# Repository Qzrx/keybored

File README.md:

# keybored
I'm bored. Let's make a keyboard!

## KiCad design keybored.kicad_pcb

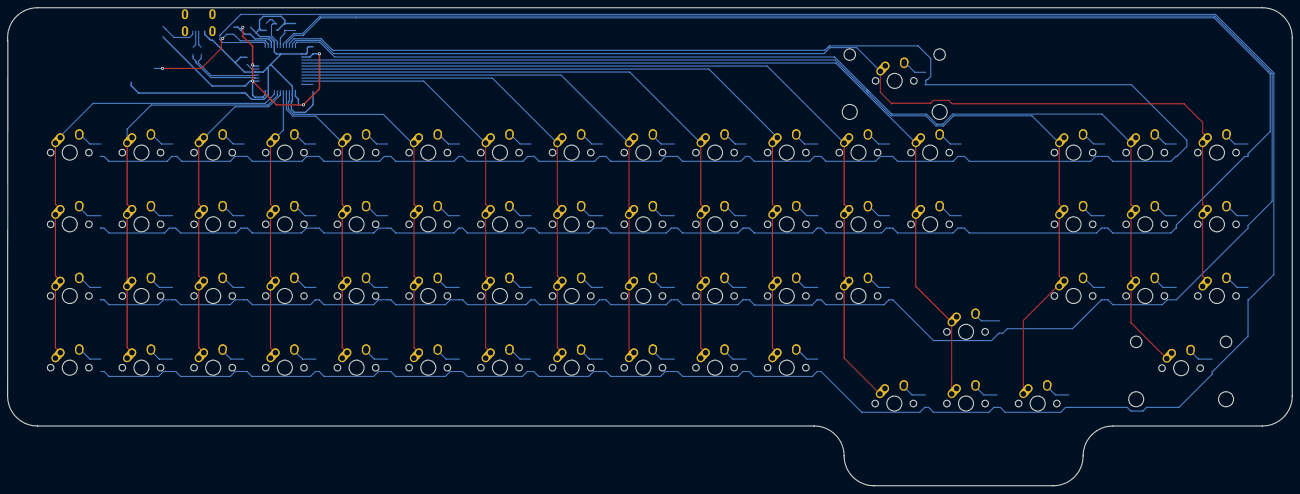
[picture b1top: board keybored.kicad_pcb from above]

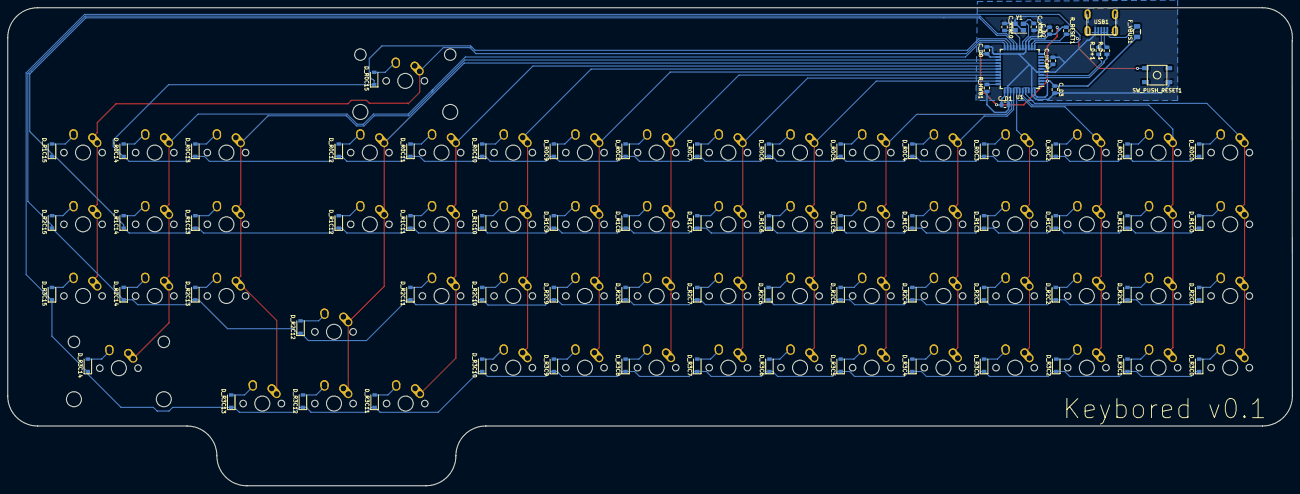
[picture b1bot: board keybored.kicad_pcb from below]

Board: 2 copper layers, 341.3 x 127.0 mm, 144 parts (80 on the bottom side), 96 nets.

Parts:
C_D0, C_D1, C_D2: 0.1uF; C_0805_2012Metric
C_D3: 10uF; C_0805_2012Metric
C_UCAP1: 1uF; C_0805_2012Metric
C_XTAL0, C_XTAL1: 22pF; C_0805_2012Metric
D_R0C0, D_R0C1, D_R0C2, D_R0C3, D_R0C4, D_R0C5, D_R0C6, D_R0C7, D_R0C8, D_R0C9, D_R0C10, D_R0C11, D_R0C12, D_R0C13, D_R0C14, D_R0C15, D_R1C0, D_R1C1, D_R1C2, D_R1C3, D_R1C4, D_R1C5, D_R1C6, D_R1C7, D_R1C8, D_R1C9, D_R1C10, D_R1C11, D_R1C12, D_R1C13, D_R1C14, D_R1C15, D_R2C0, D_R2C1, D_R2C2, D_R2C3, D_R2C4, D_R2C5, D_R2C6, D_R2C7, D_R2C8, D_R2C9, D_R2C10, D_R2C11, D_R2C12, D_R2C13, D_R2C14, D_R2C15, D_R3C0, D_R3C1, D_R3C2, D_R3C3, D_R3C4, D_R3C5, D_R3C6, D_R3C7, D_R3C8, D_R3C9, D_R3C10, D_R3C11, D_R3C12, D_R3C13, D_R3C14, D_R3C15: Diode; D_SOD-123
F_VBUS1: 500mA; Fuse_1206_3216Metric
MX_R0C0_ESC1, MX_R0C1_Q1, MX_R0C2_W1, MX_R0C3_E1, MX_R0C4_R1, MX_R0C5_T1, MX_R0C6_Y1, MX_R0C7_U1, MX_R0C8_I1, MX_R0C9_O1, MX_R0C10_P1, MX_R0C11_LBRKT1, MX_R0C12_RBRKT1, MX_R0C13_7, MX_R0C14_8, MX_R1C0_TAB1, MX_R1C1_A1, MX_R1C2_S1, MX_R1C3_D1, MX_R1C4_F1, MX_R1C5_G1, MX_R1C6_H1, MX_R1C7_J1, MX_R1C8_K1, MX_R1C9_L1, MX_R1C10_SCLN1, MX_R1C11_SQTE1, MX_R1C12_RTRN1, MX_R1C13_4, MX_R1C14_5, MX_R1C15_9, MX_R2C0_SHIFT1, MX_R2C1_Z1, MX_R2C2_X1, MX_R2C3_C1, MX_R2C4_V1, MX_R2C5_B1, MX_R2C6_N1, MX_R2C7_M1, MX_R2C8_CMMA1, MX_R2C9_PERI1, MX_R2C10_SLSH1, MX_R2C11_BSLSH1, MX_R2C12_UARR1, MX_R2C13_1, MX_R2C14_2, MX_R2C15_6, MX_R3C0_FN1, MX_R3C1_CTRLL1, MX_R3C2_ALTL1, MX_R3C3_CMDL1, MX_R3C4_LAYRD1, MX_R3C5_SPCEL1, MX_R3C6_SPCER1, MX_R3C7_LYERU1, MX_R3C8_CMDR1, MX_R3C9_ALTR1, MX_R3C10_RSHIFT1, MX_R3C11_LARR1, MX_R3C12_DARR1, MX_R3C13_RARR1, MX_R3C15_1: MX-NoLED; MX-1U-NoLED
MX_R0C15_BKSPC1, MX_R3C14_0: MX-2U-NoLED
R_D+1: 22; R_0805_2012Metric
R_D-1: 22; R_0805_2012Metric
R_HWB1: 10k; R_0805_2012Metric
R_RESET1: 10k; R_0805_2012Metric
SW_PUSH_RESET1: SW_Push; SKQG-1155865
U1: ATmega32U4-AU; TQFP-44_10x10mm_P0.8mm
USB1: Molex-0548190589
Y1: 16MHz; Crystal_SMD_3225-4Pin_3.2x2.5mm

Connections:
+5V: C_D0.1, C_D1.1, C_D2.1, C_D3.1, F_VBUS1.1, R_RESET1.1, U1.2, U1.7, U1.14, U1.24, U1.34, U1.44
COL0: MX_R0C0_ESC1.1, MX_R1C0_TAB1.1, MX_R2C0_SHIFT1.1, MX_R3C0_FN1.1, U1.41
COL1: MX_R0C1_Q1.1, MX_R1C1_A1.1, MX_R2C1_Z1.1, MX_R3C1_CTRLL1.1, U1.40
COL2: MX_R0C2_W1.1, MX_R1C2_S1.1, MX_R2C2_X1.1, MX_R3C2_ALTL1.1, U1.39
COL3: MX_R0C3_E1.1, MX_R1C3_D1.1, MX_R2C3_C1.1, MX_R3C3_CMDL1.1, U1.38
COL4: MX_R0C4_R1.1, MX_R1C4_F1.1, MX_R2C4_V1.1, MX_R3C4_LAYRD1.1, U1.37
COL5: MX_R0C5_T1.1, MX_R1C5_G1.1, MX_R2C5_B1.1, MX_R3C5_SPCEL1.1, U1.36
COL6: MX_R0C6_Y1.1, MX_R1C6_H1.1, MX_R2C6_N1.1, MX_R3C6_SPCER1.1, U1.32
COL7: MX_R0C7_U1.1, MX_R1C7_J1.1, MX_R2C7_M1.1, MX_R3C7_LYERU1.1, U1.31
COL8: MX_R0C8_I1.1, MX_R1C8_K1.1, MX_R2C8_CMMA1.1, MX_R3C8_CMDR1.1, U1.30
COL9: MX_R0C9_O1.1, MX_R1C9_L1.1, MX_R2C9_PERI1.1, MX_R3C9_ALTR1.1, U1.29
COL10: MX_R0C10_P1.1, MX_R1C10_SCLN1.1, MX_R2C10_SLSH1.1, MX_R3C10_RSHIFT1.1, U1.28
COL11: MX_R0C11_LBRKT1.1, MX_R1C11_SQTE1.1, MX_R2C11_BSLSH1.1, MX_R3C11_LARR1.1, U1.27
COL12: MX_R0C12_RBRKT1.1, MX_R1C12_RTRN1.1, MX_R2C12_UARR1.1, MX_R3C12_DARR1.1, U1.26
COL13: MX_R0C13_7.1, MX_R1C13_4.1, MX_R2C13_1.1, MX_R3C13_RARR1.1, U1.25
COL14: MX_R0C14_8.1, MX_R1C14_5.1, MX_R2C14_2.1, MX_R3C14_0.1, U1.22
COL15: MX_R0C15_BKSPC1.1, MX_R1C15_9.1, MX_R2C15_6.1, MX_R3C15_1.1, U1.21
D+: R_D+1.2, USB1.3
D-: R_D-1.2, USB1.4
GND: C_D0.2, C_D1.2, C_D2.2, C_D3.2, C_UCAP1.2, C_XTAL0.1, C_XTAL1.2, R_HWB1.1, SW_PUSH_RESET1.1, U1.5, U1.15, U1.23, U1.35, U1.43, USB1.1, Y1.2, Y1.4
unnamed: C_UCAP1.1, U1.6
unnamed: C_XTAL0.2, U1.17, Y1.1
unnamed: C_XTAL1.1, U1.16, Y1.3
unnamed: D_R0C0.2, MX_R0C0_ESC1.2
unnamed: D_R0C1.2, MX_R0C1_Q1.2
unnamed: D_R0C2.2, MX_R0C2_W1.2
unnamed: D_R0C3.2, MX_R0C3_E1.2
unnamed: D_R0C4.2, MX_R0C4_R1.2
unnamed: D_R0C5.2, MX_R0C5_T1.2
unnamed: D_R0C6.2, MX_R0C6_Y1.2
unnamed: D_R0C7.2, MX_R0C7_U1.2
unnamed: D_R0C8.2, MX_R0C8_I1.2
unnamed: D_R0C9.2, MX_R0C9_O1.2
unnamed: D_R0C10.2, MX_R0C10_P1.2
unnamed: D_R0C11.2, MX_R0C11_LBRKT1.2
unnamed: D_R0C12.2, MX_R0C12_RBRKT1.2
unnamed: D_R0C13.2, MX_R0C13_7.2
unnamed: D_R0C14.2, MX_R0C14_8.2
unnamed: D_R0C15.2, MX_R0C15_BKSPC1.2
unnamed: D_R1C0.2, MX_R1C0_TAB1.2
unnamed: D_R1C1.2, MX_R1C1_A1.2
unnamed: D_R1C2.2, MX_R1C2_S1.2
unnamed: D_R1C3.2, MX_R1C3_D1.2
unnamed: D_R1C4.2, MX_R1C4_F1.2
unnamed: D_R1C5.2, MX_R1C5_G1.2
unnamed: D_R1C6.2, MX_R1C6_H1.2
unnamed: D_R1C7.2, MX_R1C7_J1.2
unnamed: D_R1C8.2, MX_R1C8_K1.2
unnamed: D_R1C9.2, MX_R1C9_L1.2
unnamed: D_R1C10.2, MX_R1C10_SCLN1.2
unnamed: D_R1C11.2, MX_R1C11_SQTE1.2
unnamed: D_R1C12.2, MX_R1C12_RTRN1.2
unnamed: D_R1C13.2, MX_R1C13_4.2
unnamed: D_R1C14.2, MX_R1C14_5.2
unnamed: D_R1C15.2, MX_R1C15_9.2
unnamed: D_R2C0.2, MX_R2C0_SHIFT1.2
unnamed: D_R2C1.2, MX_R2C1_Z1.2
unnamed: D_R2C2.2, MX_R2C2_X1.2
unnamed: D_R2C3.2, MX_R2C3_C1.2
unnamed: D_R2C4.2, MX_R2C4_V1.2
unnamed: D_R2C5.2, MX_R2C5_B1.2
unnamed: D_R2C6.2, MX_R2C6_N1.2
unnamed: D_R2C7.2, MX_R2C7_M1.2
unnamed: D_R2C8.2, MX_R2C8_CMMA1.2
unnamed: D_R2C9.2, MX_R2C9_PERI1.2
unnamed: D_R2C10.2, MX_R2C10_SLSH1.2
unnamed: D_R2C11.2, MX_R2C11_BSLSH1.2
unnamed: D_R2C12.2, MX_R2C12_UARR1.2
unnamed: D_R2C13.2, MX_R2C13_1.2
unnamed: D_R2C14.2, MX_R2C14_2.2
unnamed: D_R2C15.2, MX_R2C15_6.2
unnamed: D_R3C0.2, MX_R3C0_FN1.2
unnamed: D_R3C1.2, MX_R3C1_CTRLL1.2
unnamed: D_R3C2.2, MX_R3C2_ALTL1.2
unnamed: D_R3C3.2, MX_R3C3_CMDL1.2
unnamed: D_R3C4.2, MX_R3C4_LAYRD1.2
unnamed: D_R3C5.2, MX_R3C5_SPCEL1.2
unnamed: D_R3C6.2, MX_R3C6_SPCER1.2
unnamed: D_R3C7.2, MX_R3C7_LYERU1.2
unnamed: D_R3C8.2, MX_R3C8_CMDR1.2
unnamed: D_R3C9.2, MX_R3C9_ALTR1.2
unnamed: D_R3C10.2, MX_R3C10_RSHIFT1.2
unnamed: D_R3C11.2, MX_R3C11_LARR1.2
unnamed: D_R3C12.2, MX_R3C12_DARR1.2
unnamed: D_R3C13.2, MX_R3C13_RARR1.2
unnamed: D_R3C14.2, MX_R3C14_0.2
unnamed: D_R3C15.2, MX_R3C15_1.2
unnamed: R_D+1.1, U1.4
unnamed: R_D-1.1, U1.3
unnamed: R_HWB1.2, U1.33
unnamed: R_RESET1.2, SW_PUSH_RESET1.2, U1.13
ROW0: D_R0C0.1, D_R0C1.1, D_R0C2.1, D_R0C3.1, D_R0C4.1, D_R0C5.1, D_R0C6.1, D_R0C7.1, D_R0C8.1, D_R0C9.1, D_R0C10.1, D_R0C11.1, D_R0C12.1, D_R0C13.1, D_R0C14.1, D_R0C15.1, U1.20
ROW1: D_R1C0.1, D_R1C1.1, D_R1C2.1, D_R1C3.1, D_R1C4.1, D_R1C5.1, D_R1C6.1, D_R1C7.1, D_R1C8.1, D_R1C9.1, D_R1C10.1, D_R1C11.1, D_R1C12.1, D_R1C13.1, D_R1C14.1, D_R1C15.1, U1.19
ROW2: D_R2C0.1, D_R2C1.1, D_R2C2.1, D_R2C3.1, D_R2C4.1, D_R2C5.1, D_R2C6.1, D_R2C7.1, D_R2C8.1, D_R2C9.1, D_R2C10.1, D_R2C11.1, D_R2C12.1, D_R2C13.1, D_R2C14.1, D_R2C15.1, U1.18
ROW3: D_R3C0.1, D_R3C1.1, D_R3C2.1, D_R3C3.1, D_R3C4.1, D_R3C5.1, D_R3C6.1, D_R3C7.1, D_R3C8.1, D_R3C9.1, D_R3C10.1, D_R3C11.1, D_R3C12.1, D_R3C13.1, D_R3C14.1, D_R3C15.1, U1.12
VCC: F_VBUS1.2, USB1.5

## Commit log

2020-09-08 first commit with project files
2020-09-08 Added submodules for kicad keyboard pcb libraries
2020-09-08 Added libraries to project in kicad
2020-09-08 I added a bunch of schematics, hoorah \!
2020-09-08 Fixed mx switch footprint to use MX-1U instead of MX-NoLED
2020-09-08 completed the v0.1 pcb design
2020-09-08 first render
2020-09-08 improved readme
2020-09-10 First commit with new layout matrix
2020-09-10 updated main board schematic
2020-09-10 new switches are now in PCB file
2020-09-11 I just wired up a 63-key board. yiiikes.
2020-09-11 wired up switches to ATMega
2020-09-11 a few extra tweeks including silkscreen color and adding ground fill
2020-09-11 Fixed up some missed connections
2020-09-11 added gitignore and gerbers
2020-09-12 moved MCU above ortho48 section
2020-09-12 always need an rt'd render of your board
2020-09-12 forgot fill zones
2020-09-12 updating fp-info-cache
2020-10-06 Added KLE JSON
2020-10-06 added plate dxf
